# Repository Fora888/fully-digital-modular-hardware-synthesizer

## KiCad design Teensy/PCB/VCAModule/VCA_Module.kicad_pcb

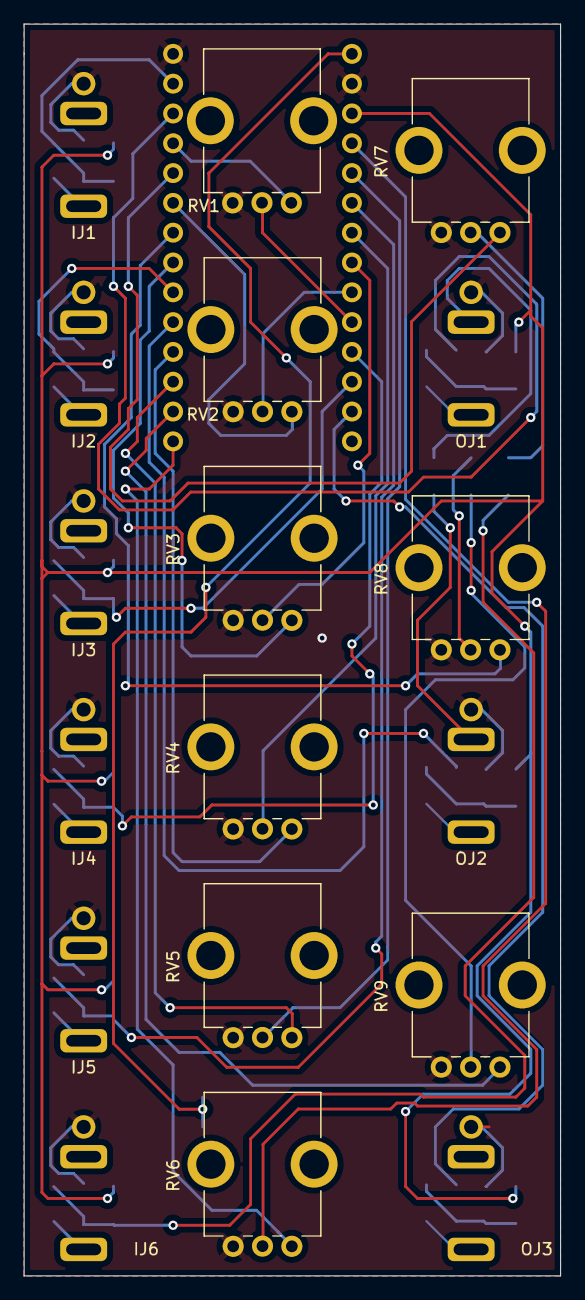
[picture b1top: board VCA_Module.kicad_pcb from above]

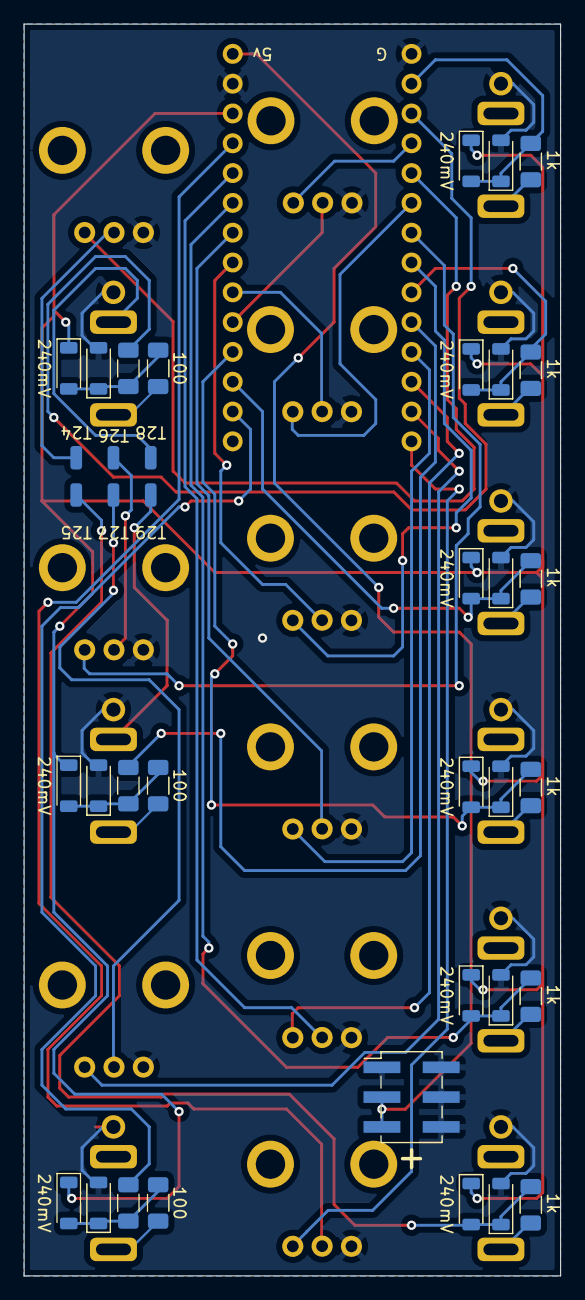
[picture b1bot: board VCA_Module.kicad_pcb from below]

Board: 2 copper layers, 45.7 x 106.7 mm, 51 parts (33 on the bottom side), 44 nets.

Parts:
ID1, ID2, ID3, ID4, ID5, ID6, ID7, ID8, ID9, ID10, ID11, ID12: 240mV; D_SOD-123 Handsolder
IJ1, IJ2, IJ3, IJ4, IJ5, IJ6: Input; 3.5mm Jack Perfboard
IR1, IR2, IR3, IR4, IR5, IR6: 1k; R_1206_3216Metric_Pad1.30x1.75mm_HandSolder
J1: Power_Connector_2x3; PinHeader_2x03_P2.54mm_Vertical_SMD
OD1, OD2, OD3, OD4, OD5, OD6: 240mV; D_SOD-123 Handsolder
OJ1, OJ2, OJ3: Input; 3.5mm Jack Perfboard
OR1, OR3, OR5: 100; R_1206_3216Metric_Pad1.30x1.75mm_HandSolder
OR2, OR4, OR6: 900; R_1206_3216Metric_Pad1.30x1.75mm_HandSolder
RV1: CV_1_Slope; Bourns_PTV09A-4020UB103
RV2: CV_Scale_1; Bourns_PTV09A-4020UB103
RV3: CV_2_Slope; Bourns_PTV09A-4020UB103
RV4: CV_Scale_2; Bourns_PTV09A-4020UB103
RV5: CV_3_Slope; Bourns_PTV09A-4020UB103
RV6: CV_Scale_3; Bourns_PTV09A-4020UB103
RV7: VCA_1_Gain; Bourns_PTV09A-4025FB103
RV8: VCA_2_Gain; Bourns_PTV09A-4025FB103
RV9: VCA_3_Gain; Bourns_PTV09A-4025FB103
U1: Teensy4.0; Teensy 4.0 horizontal
U1#2: Teensy4.0; Teensy 4.0 back pins

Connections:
+3.3V: ID2.1 (K), ID4.1 (K), ID6.1 (K), ID8.1 (K), ID10.1 (K), ID12.1 (K), OD2.1 (K), OD4.1 (K), OD6.1 (K), U1.31 (3V3)
+5V: J1.3, J1.5, U1.33 (VIN)
/T0: ID1.1 (K), ID2.2 (A), IR1.2, U1.2 (0_RX1_CRX2_CS1)
/T1: OR2.2, U1.3 (1_TX1_CTX2_MISO1)
/T2: RV1.1, U1.4 (2_OUT2)
/T3: RV7.1, U1.5 (3_LRCLK2)
/T4: RV2.1, U1.6 (4_BCLK2)
/T5: RV8.1, U1.7 (5_IN2)
/T6: RV3.1, U1.8 (6_OUT1D)
/T7: ID3.1 (K), ID4.2 (A), IR2.2, U1.9 (7_RX2_OUT1A)
/T8: OR4.2, U1.10 (8_TX2_IN1)
/T9: RV4.1, U1.11 (9_OUT1C)
/T10: RV5.1, U1.12 (10_CS_MQSR)
/T11: RV9.1, U1.13 (11_MOSI_CTX1)
/T12: RV6.1, U1.14 (12_MISO_MQSL)
/T14: OR6.2, U1.21 (14_A0_TX3_SPDIF_OUT)
/T15: ID5.1 (K), ID6.2 (A), IR3.2, U1.22 (15_A1_RX3_SPDIF_IN)
/T16: ID7.1 (K), ID8.2 (A), IR4.2, U1.23 (16_A2_RX4_SCL1)
/T17: RV1.2, U1.24 (17_A3_TX4_SDA1)
/T18: RV2.2, U1.25 (18_A4_SDA0)
/T19: RV3.2, U1.26 (19_A5_SCL0)
/T20: RV4.2, U1.27 (20_A6_TX5_LRCLK1)
/T21: ID9.1 (K), ID10.2 (A), IR5.2, U1.28 (21_A7_RX5_BCLK1)
/T22: RV5.2, U1.29 (22_A8_CTX1)
/T23: RV6.2, U1.30 (23_A9_CRX1_MCLK1)
/T24: RV7.2, U1#2.35 (24_A10_TX6_SCL2)
/T25: ID11.1 (K), ID12.2 (A), IR6.2, U1#2.36 (25_A11_RX6_SDA2)
/T26: RV8.2, U1#2.37 (26_A12_MOSI1)
/T27: RV9.2, U1#2.38 (27_A13_SCK1)
/T28: OJ1.S, U1#2.39 (28_RX7)
/T29: OJ2.S, U1#2.40 (29_TX7)
GND: ID1.2 (A), ID3.2 (A), ID5.2 (A), ID7.2 (A), ID9.2 (A), ID11.2 (A), IJ1.G, IJ2.G, IJ3.G, IJ4.G, IJ5.G, IJ6.G, J1.1, J1.2, J1.4, J1.6, OD1.2 (A), OD3.2 (A), OD5.2 (A), OJ1.G, OJ2.G, OJ3.G, RV1.3, RV2.3, RV3.3, RV4.3, RV5.3, RV6.3, RV7.3, RV8.3, RV9.3, U1.1 (GND), U1.32 (GND)
unnamed: IJ1.T, IR1.1
unnamed: IJ2.T, IR2.1
unnamed: IJ3.T, IR3.1
unnamed: IJ4.T, IR4.1
unnamed: IJ5.T, IR5.1
unnamed: IJ6.T, IR6.1
unnamed: OD1.1 (K), OD2.2 (A), OR1.2, OR2.1
unnamed: OD3.1 (K), OD4.2 (A), OR3.2, OR4.1
unnamed: OD5.1 (K), OD6.2 (A), OR5.2, OR6.1
unnamed: OJ1.T, OR1.1
unnamed: OJ2.T, OR3.1
unnamed: OJ3.T, OR5.1
